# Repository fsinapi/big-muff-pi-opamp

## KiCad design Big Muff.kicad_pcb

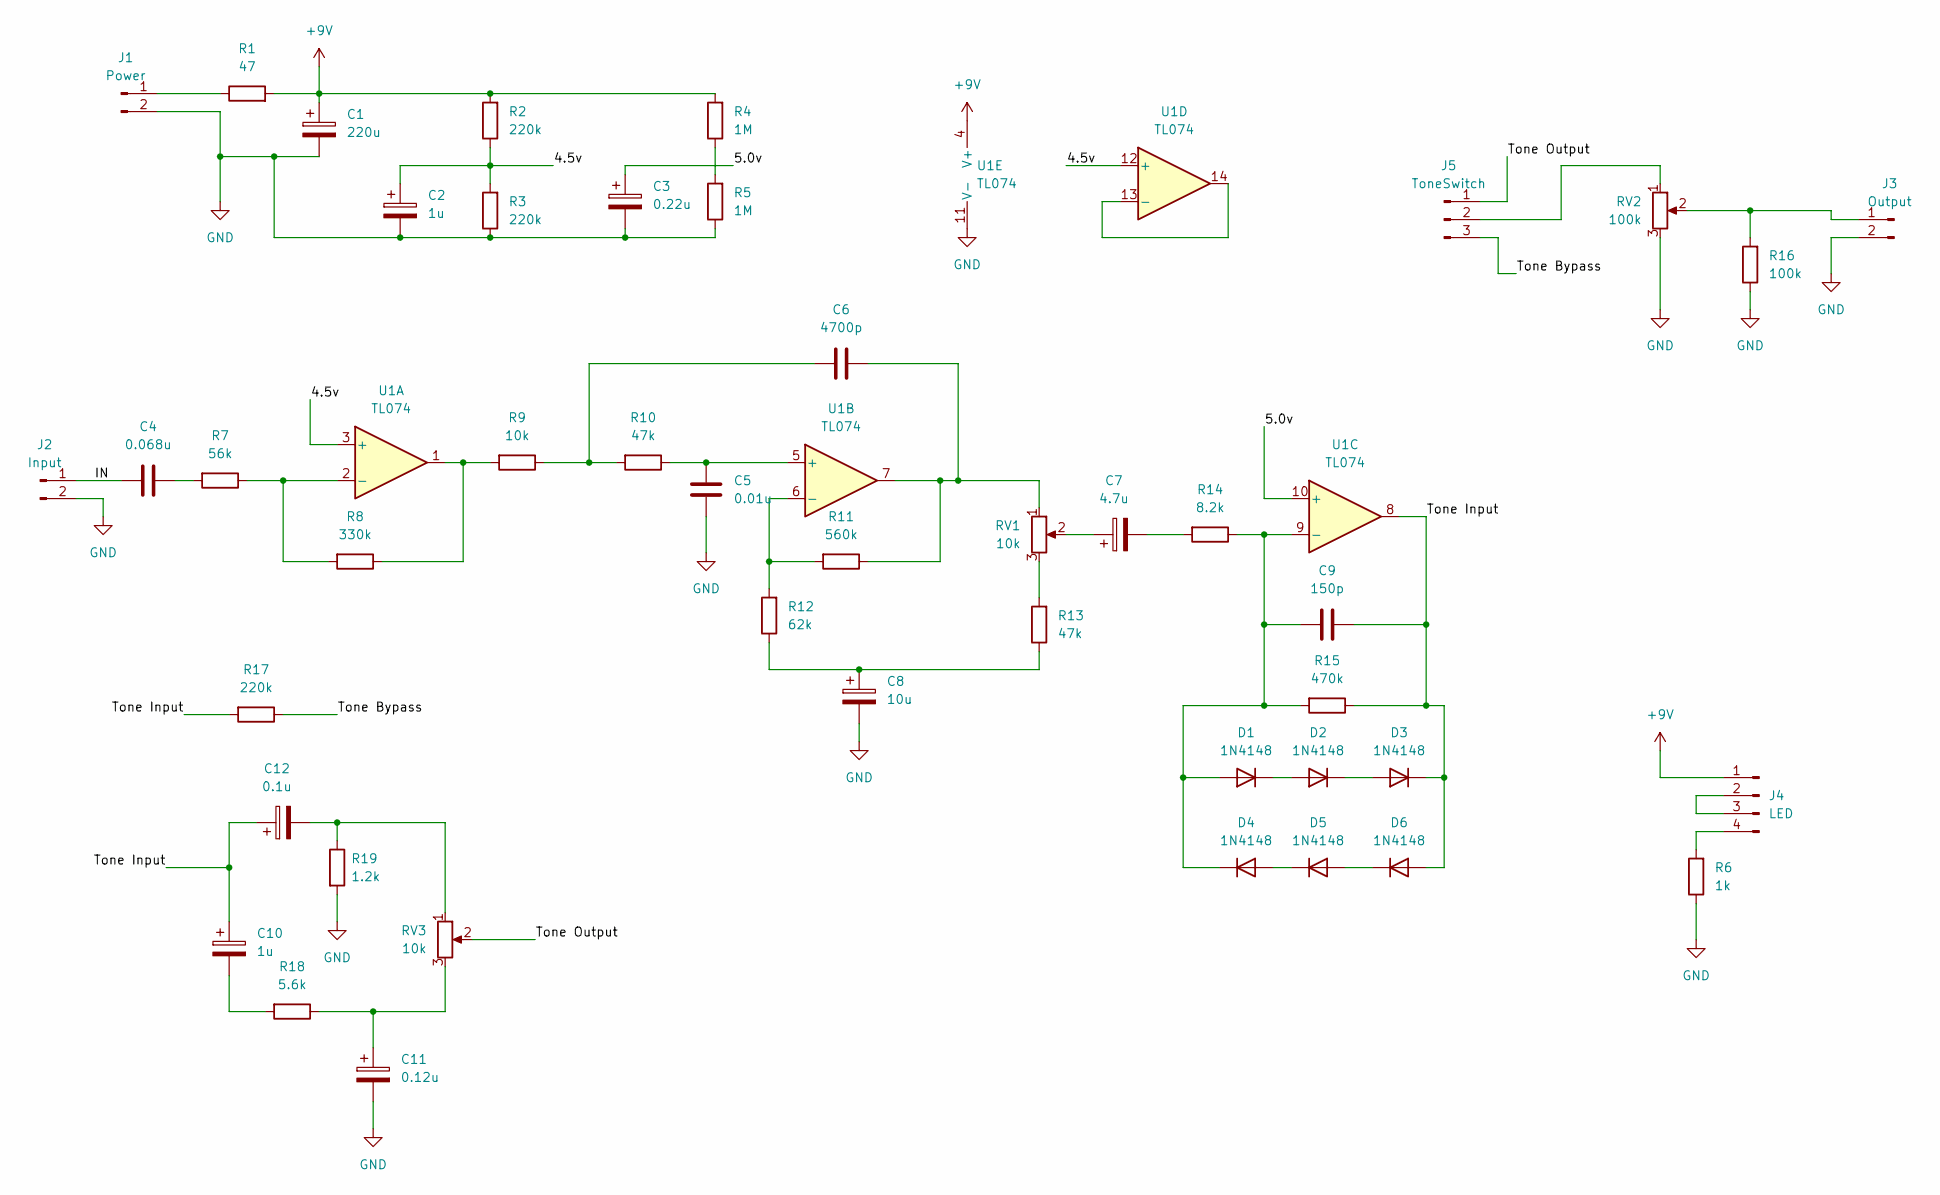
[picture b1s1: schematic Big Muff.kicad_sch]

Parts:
C1: 220u; CP_Radial_D5.0mm_P2.50mm
C2, C10: 1u; CP_Radial_D5.0mm_P2.50mm
C3: 0.22u; CP_Radial_D5.0mm_P2.50mm
C4: 0.068u; C_Rect_L7.0mm_W2.0mm_P5.00mm
C5: 0.01u; C_Rect_L7.0mm_W2.0mm_P5.00mm
C6: 4700p; C_Rect_L4.0mm_W2.5mm_P2.50mm
C7: 4.7u; CP_Radial_D5.0mm_P2.50mm
C8: 10u; CP_Radial_D5.0mm_P2.50mm
C9: 150p; C_Rect_L4.0mm_W2.5mm_P2.50mm
C11: 0.12u; CP_Radial_D5.0mm_P2.50mm
C12: 0.1u; CP_Radial_D5.0mm_P2.50mm
D1, D2, D3, D4, D5, D6: 1N4148; D_DO-35_SOD27_P7.62mm_Horizontal
J1: Power; PinHeader_1x02_P2.54mm_Vertical
J2: Input; PinHeader_1x02_P2.54mm_Vertical
J3: Output; PinHeader_1x02_P2.54mm_Vertical
J4: LED; PinHeader_1x04_P2.54mm_Vertical
J5: ToneSwitch; PinHeader_1x03_P2.54mm_Vertical
R1: 47; R_Axial_DIN0204_L3.6mm_D1.6mm_P7.62mm_Horizontal
R2, R3, R17: 220k; R_Axial_DIN0204_L3.6mm_D1.6mm_P7.62mm_Horizontal
R4, R5: 1M; R_Axial_DIN0204_L3.6mm_D1.6mm_P7.62mm_Horizontal
R6: 1k; R_Axial_DIN0204_L3.6mm_D1.6mm_P7.62mm_Horizontal
R7: 56k; R_Axial_DIN0204_L3.6mm_D1.6mm_P7.62mm_Horizontal
R8: 330k; R_Axial_DIN0204_L3.6mm_D1.6mm_P7.62mm_Horizontal
R9: 10k; R_Axial_DIN0204_L3.6mm_D1.6mm_P7.62mm_Horizontal
R10, R13: 47k; R_Axial_DIN0204_L3.6mm_D1.6mm_P7.62mm_Horizontal
R11: 560k; R_Axial_DIN0204_L3.6mm_D1.6mm_P7.62mm_Horizontal
R12: 62k; R_Axial_DIN0204_L3.6mm_D1.6mm_P7.62mm_Horizontal
R14: 8.2k; R_Axial_DIN0204_L3.6mm_D1.6mm_P7.62mm_Horizontal
R15: 470k; R_Axial_DIN0204_L3.6mm_D1.6mm_P7.62mm_Horizontal
R16: 100k; R_Axial_DIN0204_L3.6mm_D1.6mm_P7.62mm_Horizontal
R18: 5.6k; R_Axial_DIN0204_L3.6mm_D1.6mm_P7.62mm_Horizontal
R19: 1.2k; R_Axial_DIN0204_L3.6mm_D1.6mm_P7.62mm_Horizontal
RV1, RV3: 10k; Potentiometer_Vishay_T73XW_Horizontal
RV2: 100k; Potentiometer_Vishay_T73XW_Horizontal
U1: TL074; DIP-14_W7.62mm

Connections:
+9V: C1.1, J4.1, R1.2, R2.2, R4.2, U1.4 (V+)
/4.5v: C2.1, R2.1, R3.2, U1.3 (+), U1.12 (+)
/5.0v: C3.1, U1.10 (+)
/IN: C4.1, J2.1
/Tone Bypass: J5.3, R17.1
/Tone Input: C9.2, C10.1, C12.1, D3.1 (K), D6.2 (A), R15.1, R17.2, U1.8
/Tone Output: J5.1, RV3.2
GND: C1.2, C2.2, C3.2, C5.2, C8.2, C11.2, J1.2, J2.2, J3.2, R3.1, R5.1, R6.1, R16.1, R19.2, RV2.3, U1.11 (V-)
unnamed: C4.2, R7.2
unnamed: C6.1, R9.1, R10.2
unnamed: C6.2, R11.1, RV1.1, U1.7
unnamed: C7.1, RV1.2
unnamed: C7.2, R14.2
unnamed: C8.1, R12.1, R13.1
unnamed: C10.2, R18.2
unnamed: C11.1, R18.1, RV3.3
unnamed: C12.2, R19.1, RV3.1
unnamed: C9.1, D1.2 (A), D4.1 (K), R14.1, R15.2, U1.9 (-)
unnamed: D1.1 (K), D2.2 (A)
unnamed: D2.1 (K), D3.2 (A)
unnamed: D4.2 (A), D5.1 (K)
unnamed: D5.2 (A), D6.1 (K)
unnamed: J1.1, R1.1
unnamed: J3.1, R16.2, RV2.2
unnamed: J4.2, J4.3
unnamed: J4.4, R6.2
unnamed: J5.2, RV2.1
unnamed: R4.1, R5.2
unnamed: R8.1, R9.2, U1.1
unnamed: R13.2, RV1.3
unnamed: R7.1, R8.2, U1.2 (-)
unnamed: C5.1, R10.1, U1.5 (+)
unnamed: R11.2, R12.2, U1.6 (-)
unnamed: U1.13 (-), U1.14

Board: 2 copper layers, 46 parts (0 on the bottom side), 34 nets, no tracks yet.
